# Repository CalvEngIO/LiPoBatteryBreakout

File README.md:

# LiPoBatteryBreakout
Simple breakout for connecting a LiPo battery to a breadboard

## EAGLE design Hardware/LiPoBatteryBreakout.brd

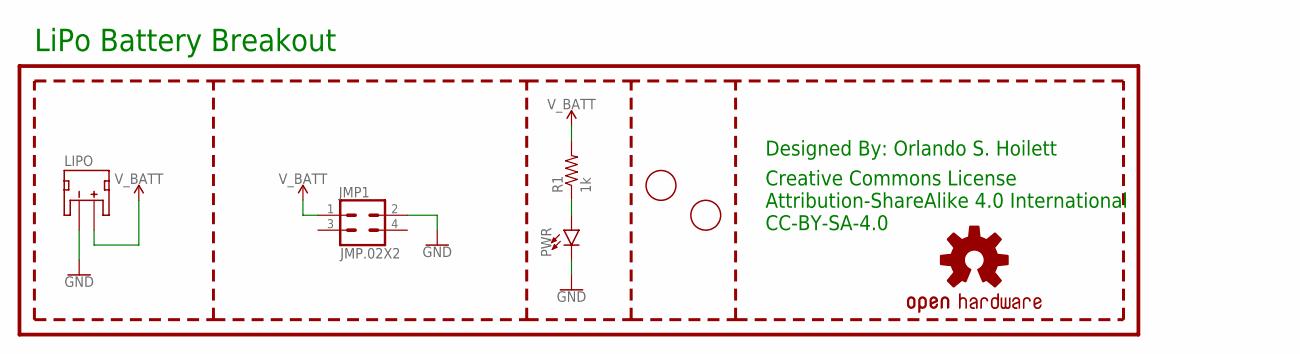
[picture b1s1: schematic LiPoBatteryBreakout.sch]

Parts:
FD1, FD2: FIDUCIAL; FIDUCIAL_1MM
JMP1: JMP.02X2
LIPO: JST_2MM_MALE; JST-2-SMD
LOGO1: OSHW-LOGOS; OSHW-LOGO-S
PWR: LED0603; LED-0603
R1: 1k; R0402
U$2: LOGO.05

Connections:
GND: JMP1.2, LIPO.1 (-), PWR.C
unnamed: PWR.A, R1.1
V_BATT: JMP1.1, LIPO.2 (+), R1.2

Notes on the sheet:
Creative Commons License Attribution-ShareAlike 4.0 International CC-BY-SA-4.0
Designed By: Orlando S. Hoilett
LiPo Battery Breakout

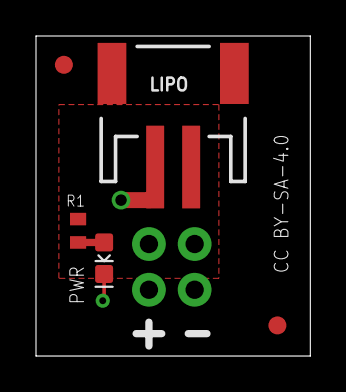
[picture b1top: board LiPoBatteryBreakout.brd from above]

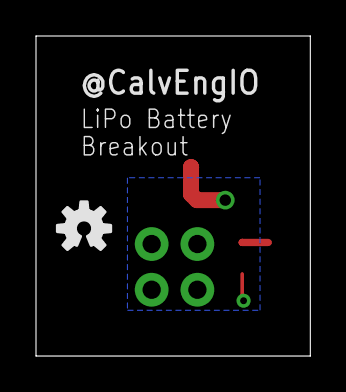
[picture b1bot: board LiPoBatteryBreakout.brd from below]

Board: 2 copper layers, 15.2 x 17.8 mm, 8 parts (2 on the bottom side), 3 nets.

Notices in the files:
parts and their libraries:
SparkFun-Connectors: Licensing: Creative Commons ShareAlike 4.0 International - https://creativecommons.org/licenses/by-sa/4.0
